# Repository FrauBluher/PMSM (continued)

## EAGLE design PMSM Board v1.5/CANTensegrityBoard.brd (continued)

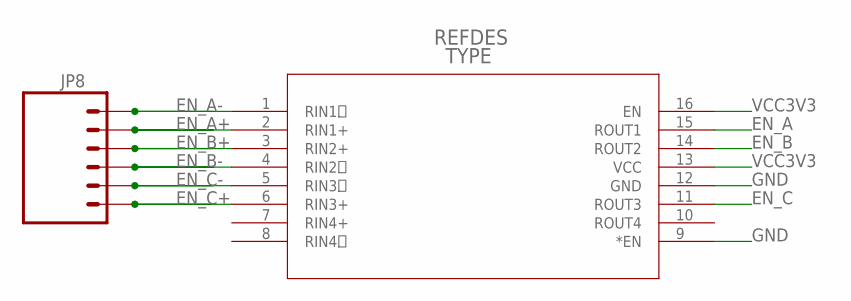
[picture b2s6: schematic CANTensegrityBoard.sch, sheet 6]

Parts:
JP8: M06SIP_LOCK; 1X06-SIP_LOCK
U3: SN65LVDT348_PW_1; PW16

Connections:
EN_A: U3.15 (ROUT1); also elsewhere on the board
EN_A+: JP8.2, U3.2 (RIN1+)
EN_A-: JP8.1, U3.1 (RIN1)
EN_B: U3.14 (ROUT2); also elsewhere on the board
EN_B+: JP8.3, U3.3 (RIN2+)
EN_B-: JP8.4, U3.4 (RIN2)
EN_C: U3.11 (ROUT3); also elsewhere on the board
EN_C+: JP8.6, U3.6 (RIN3+)
EN_C-: JP8.5, U3.5 (RIN3)
GND: U3.9 (*EN), U3.12 (GND); also elsewhere on the board
VCC3V3: U3.13 (VCC), U3.16 (EN); also elsewhere on the board

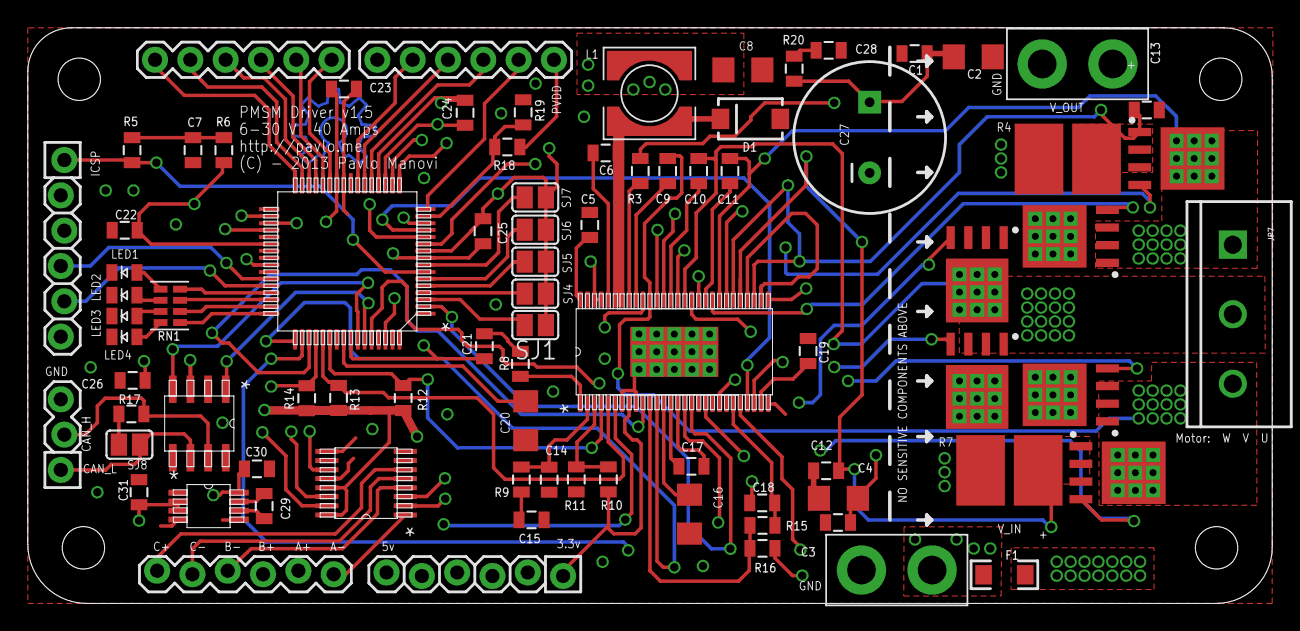
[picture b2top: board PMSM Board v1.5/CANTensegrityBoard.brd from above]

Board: 4 copper layers, 89.5 x 41.4 mm, 87 parts (0 on the bottom side), 94 nets.

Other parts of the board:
E$1, E$2, E$3, E$4: STAND-OFF-TIGHT

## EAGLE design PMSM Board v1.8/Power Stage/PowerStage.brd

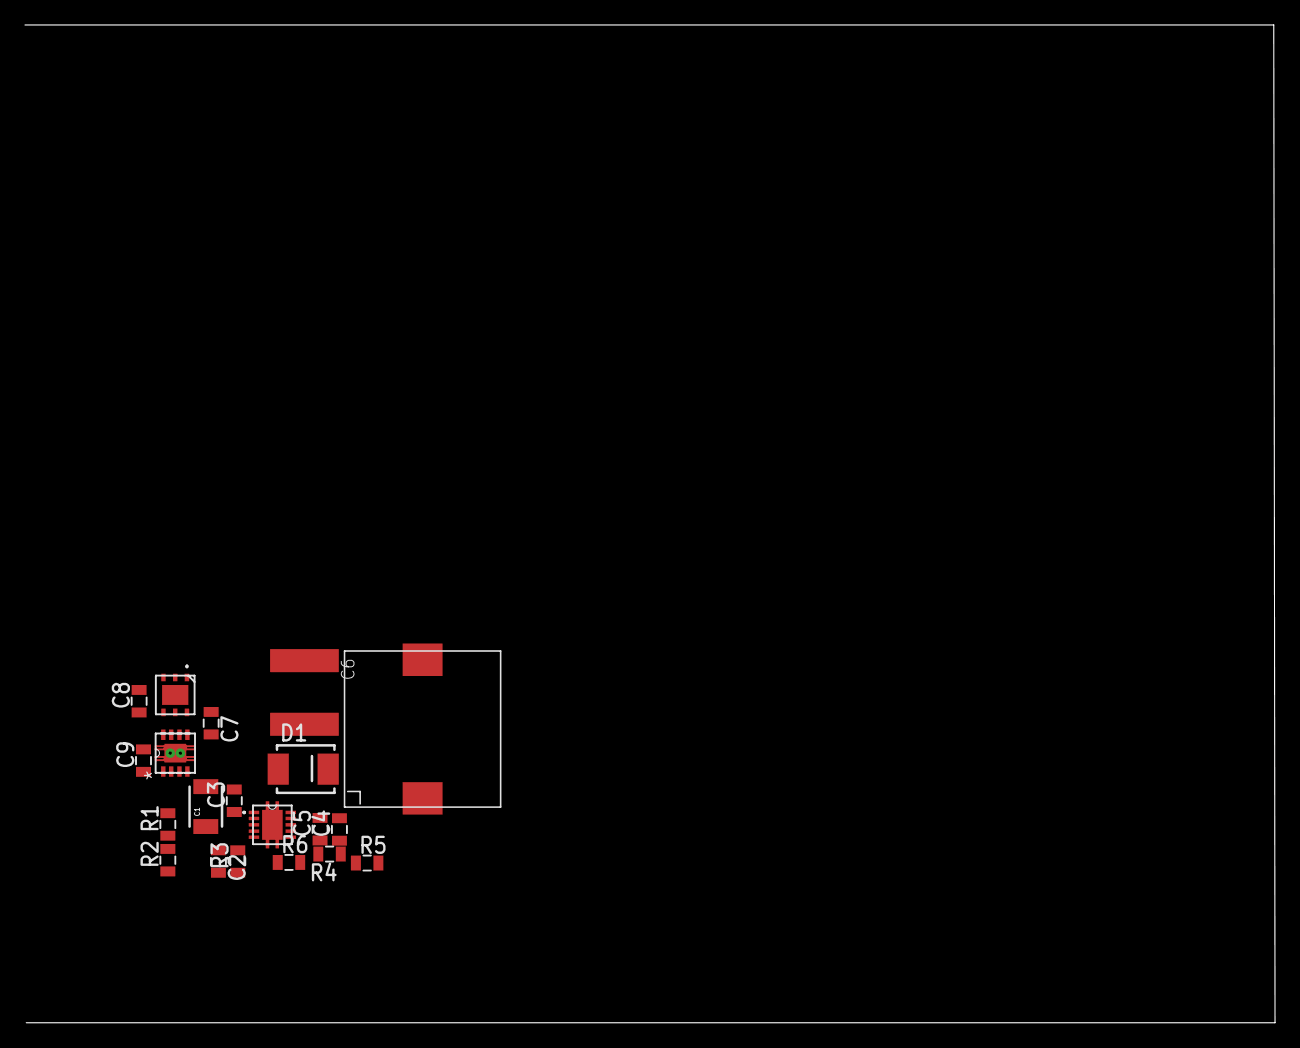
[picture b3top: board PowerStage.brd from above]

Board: 2 copper layers, 100.1 x 79.9 mm, 20 parts (0 on the bottom side), 13 nets, no tracks yet.

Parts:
C1: 4.7uF; 1210
C2: .01uF; 0805
C3: .1uF; 0805
C4: 5600pF; 0805
C5: 270pF; 0805
C6: 47uF\; C2220K
C7, C8, C9: 1uF; 0805
D1: DIODE-SCHOTTKY240A; SMA-DIODE-B240A
R1: 348k; 0805
R2: 88.7k; 0805
R3: 237k; 0805
R4: 7.68k; 0805
R5: 59k; 0805
R6: 10k; 0805
U1: TPS73733-Q1_DRB_8; DRB8_1P75X1P5
U2: TPS54240_DRC_10; DRC10_2P4X1P65
U3: LP38692_NGG_6; SDE06A
U$1: SLF12555T; SLF12555

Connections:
GND: C1.2, C2.2, C4.2, C5.2, C6.2, C7.2, C8.2, C9.2, D1.A, R2.1, R3.1, R6.1, U1.4, U1.9, U2.9, U2.P$1, U2.P$2, U2.P$3, U2.P$4, U2.P$5, U3.2, U3.7
unnamed: R1.1, R2.2, U2.3
unnamed: C2.1, U2.4
unnamed: R3.2, U2.5
unnamed: C3.1, U2.1
unnamed: C3.2, D1.C, U2.10, U$1.P$1
unnamed: C5.1, R4.2, U2.8
unnamed: C4.1, R4.1
unnamed: R5.1, R6.2, U2.7
PVDD: C1.1, R1.2, U2.2
VCC3V3: C9.1, U1.1
VCC5V0: C8.1, U1.5, U1.8, U3.4, U3.5
VCC5V5: C6.1, C7.1, R5.2, U3.1, U3.3, U3.6, U$1.P$2

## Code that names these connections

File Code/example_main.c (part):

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 * dsPIC33EP256MC506:
 *
 * - PIN FUNCTIONS - PIN # - USAGE
 * - RPI44/PWM2H/RB12 - Pin 62 - PWM2
 * - RP42/PWM3H/RB10 - Pin 60 - PWM3
 * - RP97/RF1 - PIN 59 - CANTX (VIA PPS)
 * - RPI96/RF0 - PIN 58 - CANRX (VIA PPS)
 * - RD6 - PIN 54 - PWRGD
 * - RD5 - PIN 53 - OCTW
 * - RP56/RC8 - PIN 52 - FAULT
 * - RP55/RC7 - PIN 51 - GAIN
 * - RP54/RC6 - PIN 50 - EN_GATE
 * - TMS/ASDA1/RP41/RB9 - PIN 49 - DC_CAL
 * - TP40/T4CK/ACL1/RB8 - PIN 48 - LED1
 * - RC13 - PIN 47 - LED2
 * - RP39/INT0/RB7 - PIN 46 - LED3
 * - RPI58/RC10 - PIN 45 - LED4
 * - PGEC2/RP38/RB6 - PIN 44 - PGC
 * - PGED2/RP37/RB5 - PIN 43 - PGD
 * - SDA1/RPI52/RC4 - PIN 36 - EN_A
 * - SCK1/RPI51/RC3 - PIN 35 - EN_B
 * - SDI1/RPI25/RA9 - PIN 34 - EN_C
 * - RPI46/PWM1H/RB14 - PIN 2 - PWM1
 * - AN0/OA2OUT/RA0 - PIN 13 - CRNT1 (Current Sens)
 * - AN1/C2IN1+/RA1 - PIN 14 - CRNT2 (Current Sens)
 *
 *
 * Pins connected to solderjumpers allow for specific ID's to be set on a CAN network with
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 * The following pins and peripherals are available on headers JP1, JP2, and JP5:
 *
 * - PIN FUNCTIONS - PIN # - HEADER,#
 * - AN10/RPI28/RA12 - PIN 11 - JP5,2
 * - AN8/RPI27/RA11 - PIN 12 - JP5,3
 * - AN4/RPI34/RB2 - PIN 17 - JP5,4
 * - AN5/RP35/RB3 - PIN 18 - JP5,5
 *
 * - AN3/OA1OUT/RPI33/STED1/RB1 - PIN 16 - JP2,2
 * - AN6/OA3OUT/C4IN1+/OCFB/RC0 - PIN 21 - JP2,3
 * - AN7/C3IN1-/C4IN1+/RC1 - PIN 22 - JP2,4
 * - AN8/C3IN1+/Y1RTS/BCLK1/FLT3/RC2 - PIN 23 - JP2,5
 *
 * - AN12/C2IN2-/U2RTS/BCLK2/RE12 - PIN 27 - JP1,1
 * - AN13/C3IN20/U2CTS/RE13 - PIN 28 - JP1,2
 * - AN14/RPI94/RE14 - PIN 29 - JP1,3
 * - AN14/RPI95/RE15 - PIN 30 - JP1,4
 * - SDA2/RPI24/RA8 - PIN 31 - JP1,5
 * - FLT32/SCL2/RPI36/RB4 - PIN 32 - JP1,6
 *
 * --Note: RPIx pins can only be remapped to be a peripheral input, while RPx function as I/O.
 */
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#include <stdlib.h>
#include "PMSM.h"

#define LED1 LATBbits.LATB8
#define LED2 LATCbits.LATC13
#define LED3 LATBbits.LATC7
#define LED4 LATCbits.LATC10

#if defined(__dsPIC33EP256MC506__)
_FOSCSEL(FNOSC_FRC & IESO_OFF);
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}

void DigitalPinsInit() {
    TRISDbits.TRISD6 = 1; // PWRGD
    TRISDbits.TRISD5 = 1; // OCTW
    TRISCbits.TRISC8 = 1; // FAULT
    TRISCbits.TRISC7 = 0; // GAIN
    TRISCbits.TRISC6 = 0; // EN_GATE
    TRISBbits.TRISB9 = 0; // DC_CAL
    TRISBbits.TRISB8 = 0; // LED1
    TRISCbits.TRISC13 = 0; // LED2
    TRISBbits.TRISB7 = 0; // LED3
    TRISCbits.TRISC10 = 0; // LED4
    TRISBbits.TRISB14 = 0; // PWM1 Out
    TRISBbits.TRISB12 = 0; // PWM2 Out
    TRISBbits.TRISB10 = 0; // PWM3 Out
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
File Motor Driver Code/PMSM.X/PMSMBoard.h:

/* 
 * File:   PMSMBoard.h
 * Author: Pavlo
 *
 * Created on October 29, 2013, 4:55 PM
 */


#ifndef PMSMBOARD_H
#define	PMSMBOARD_H

#include <xc.h>

#ifdef __33EP256MU806_H
/**
 * @brief Gate Duty Cycle Mapping
 */
#define GL_A_DC       SDC3
#define GH_A_DC       PDC3
#define	GL_B_DC       SDC2
#define GH_B_DC       PDC2
#define GL_C_DC       SDC1
#define GH_C_DC       PDC1

#define TRIS_EN_GATE  TRISGbits.TRISG7
#define TRIS_DC_CAL   TRISEbits.TRISE6
#define TRIS_CS       TRISGbits.TRISG9

#define TRIS_HALL1    TRISCbits.TRISC14
#define TRIS_HALL2    TRISCbits.TRISC13
#define TRIS_HALL3    TRISDbits.TRISD0

#define TRIS_LED1     TRISBbits.TRIB8
#define TRIS_LED2     TRISBbits.TRIB9
#define TRIS_LED3     TRISBbits.TRIB10
#define TRIS_LED4     TRISBbits.TRIB11

#define EN_GATE  LATGbits.LATG7
#define DC_CAL   LATGbits.LATE6
#define CS       LATGbits.LATG9

#define HALL1    PORTCbits.RC14
#define HALL2    PORTCbits.RC13
#define HALL3    PORTDbits.RD0

#define LED1     LATBbits.LATB8
#define LED2     LATBbits.LATB9
#define LED3     LATBbits.LATB10
#define LED4     LATBbits.LATB11
#endif

void UART2Init();
void ClockInit();
void MotorInit();
void TimersInit();
void PinInit();

#endif	/* PMSMBOARD_H */

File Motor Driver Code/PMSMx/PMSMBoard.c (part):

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            CS = 1;
        }
        
        EN_GATE = 0;
        uint16_t i;
        for (i = 0; i < 2000; i++) {
            Nop(); //Let the DRV catch its breath...
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    PTCON = 0x8000;

#endif
    EN_GATE = 1;
    DC_CAL = 0;

    initInfo.MotorInited = 1;
}
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}

void PinInit(void) {
    TRISDbits.TRISD7 = 1; //QEI_A
    TRISDbits.TRISD6 = 1; //QEI_B
    TRISDbits.TRISD5 = 1; //QEI_C

    // 0 - Output, 1 - Input
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
void CNInit(void) {
    //Set up Change Notify Interrupt
    CNENCbits.CNIEC14 = 1; // Enable RC14 pin for interrupt detection
    CNENCbits.CNIEC13 = 1; // Enable RC13
    CNENDbits.CNIED0 = 1;

    IEC1bits.CNIE = 1; // Enable CN interrupts
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
    //AD1CSSH/AD1CSSL: Analog-to-Digital Input Scan Selection Register
    AD1CSSH = 0x0000;
    //AD1CSSLbits.CSS1 = 1;  //PVDD MONITORING
    AD1CSSLbits.CSS12 = 1;
    AD1CSSLbits.CSS13 = 1;

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
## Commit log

2013-07-31 Update LICENSE
2013-08-06 Fixed power and ground issue on the decoupling caps
2013-09-04 Refactored some code and added a boilerplate to work off of.
2013-09-04 Update example_main.c
    Added some suggestions.
2013-09-24 Redesign of board to incorporate new TI rec. design, added filtering.
2013-09-24 Added some test points and cleaned up v1.6
2013-09-25 Removed thermals in a few places.
2013-10-01 Generated gerbers and moved a power trace.
2013-10-29 Working copy backup. Started some serious software driver/integration work.
2013-10-30 Made everything more modular and added DRV8301 Driver Code.
2014-01-07 1.7 Progress
2014-01-07 Power Stage Folder added to version 1.7 Folder
2014-01-08 More switcher work.
2014-01-10 rerouting PMSM Board
2014-01-10 Started making room for connectors
2014-01-10 More redesign work for v1.7
2014-01-13 Almost done with v1.7~
2014-01-13 Finished v1.7
2014-01-13 Choring up the repo.
2014-01-13 Added DRV830x Library
2014-01-13 Fixed CAN Connector Pinout
2014-01-13 Fixed Optical Encoder Output
2014-02-12 Fixed file paths.
2014-03-04 Choring up code for v1.7.
2014-03-11 SPI Library now works and is 100% tested for drv8303
2014-03-22 v1.7 Basic Functionality Snapshot
2014-05-07 Started board version 1.8
2014-05-08 Completed v1.8 of PMSM Board.
2014-06-24 Completed Board v1.9
2014-07-11 Motor control work and board dimension corrections.
2014-07-23 Config Tool and Code Cleanup
2014-08-03 Controls work.
2014-08-04 Embedded matplotlib into the config tool.
2014-08-18 Board v1.9b and SystemID work.
2014-08-20 Added working LQG controller for Maxon Motor
2014-09-02 Lots of FOC work.
2014-09-02 FOC working.
2014-09-03 More FOC Work.
2014-09-08 Added CAN testing project to verify the operation of the CAN modules.
2014-09-09 This holds a working copy of Motor Board Testing Can project
2014-09-09 Added the Can Festival Code base for working CAN testing code
2014-09-10 CAN Festival now working in CAN example code.
2014-09-19 Working LQG Position Control.
2014-09-20 CAN working on MOTOR board
2014-09-21 Updated PMSM.c with LQG Controller.
2014-09-21 Trying to merge with master....
2014-09-22 Code Styling, Documentation.
2014-09-23 PMSM.c Compiles.
2014-09-23 Updated some documentation.
2014-09-24 testing the new Postition controller seems to not be working properly?
2014-09-24 Added theta1 for PMSM_Init
2014-09-24 Chaned the PMSM.c file to work with Motor 7 Hopefully this will work on the other motors?
2014-09-24 Modified PMSM code to compile with CAN (again) - Haven't tested yet on this commit
2014-09-24 Added the pin defines for CAN1 on the PIC.
2014-09-28 Modified to start controlling the motor over can
2014-09-28 Added cable length and velocity methods. Event loops runs at 15kHz now.
2014-09-28 Added QEI Update to event loop.
2014-09-28 started implementing an impedance controller on the motor board
2014-09-29 Still implementing a impedence contoller.... not done yet
2014-09-29 added a .gitignore file to the project. It doesn't work retro-actively, but can be used to update the system later on Will effect newly added files
2014-09-29 Added my folder which the CAN_Testing branch uses. This project will not compile correctly if you are not on the CAN_Testing Branch
2014-10-01 Working on a impedance controller, this has an OK(?) PD controller on motor
2014-10-01 Kind of works... I think. Oscillates a lot, but does what I think it should do??
2014-10-01 Working on figuring out a QEI issue
2014-10-02 Trying to make something work on controls
2014-10-02 Got rid of some junk files with a .*~ ending.
2014-10-02 Messing with intial parameters
2014-10-02 Pavlo worked on getting DRV error codes to output over UART
2014-10-06 Remved all the MPLabX build files from PMSMx's index
2014-10-06 Removed all the text editor backup files (~) from the repo
2014-10-06 Edited the old code that cropped up in merger..... :-/
2014-12-02 Re-ID of motors and state-space implementation of controls.
2014-12-11 Major Refactor, new Controllers Pos/Vel, documentation needs updating.
2015-02-04 Changes made a while ago for the CANTesting branch
2015-02-05 disabled config settings to allow the code to be used with a bootloader
2015-02-05 Modified the CAN objectdic files
2015-02-05 Changed the #include to correct path for data.h in objectdic.h
2015-02-05 Changed the naming for CAN motor position variable
2015-02-06 Stuff
2015-02-07 EN_GATE refactoring.
2015-02-07 Stopped tracking compiled files.
2015-02-13 Working on getting Torque controll
2015-02-13 Added an updated object dictionary for CANOpen
2015-02-13 Added CAN Impdeance characterization stuff
2015-02-13 Added PRBSData.h
2015-02-17 Working to get ICRA data
2015-02-19 Modified code to accept position data from ROS network with consisten units as it outputs milli-radians
2015-02-20 SStuff
2015-02-20 Lowered PWM frequency, and modified dead-time correction settings.
2015-02-20 Modified for new Position Controller testing
2015-02-21 New position controller.
2015-02-21 Another new motor position controller.
2015-02-21 Motor Board proportional controller.
2015-02-23 Revert "Another new motor position controller."
    This reverts commit 22a5d82d473f195f83678fc6334c705e9404d4e3.
2015-02-24 Added new objdict files for Motor Boards 2 and 72
2015-02-24 Updating canopen files
2015-02-25 Changed the CAN objdict files
2015-02-26 Updated the objdict files
2015-02-26 new objcdict stuff
2015-02-26 This code works without CAN....
2015-02-26 Works with CAN!
2015-02-26 Now working with config builds for 2 and 72 boards
2015-02-26 Updated heartbeat messages in objdict
2015-03-06 Changes to the can controller and the CANOpen files
2015-03-06 Decoupled commuation and control.
2015-03-06 Added objdict 72 files
2015-03-07 CLID Work.
2015-03-07 Changed objdict for Motor testing
2015-03-07 Code now compiles.
2015-03-09 Updated the latest code with the new CANOpen Objdicts
2015-03-09 Switched from testing data to position
2015-03-09 Updated the .h objdict 2
2015-03-09 Trying to figure out why Position isn't working
2015-03-19 Modified the motor controller to be a P gain controller. Also updating commutation at controller update speed, not 15kHz.
2015-04-08 WOrking on impedance controller
2015-04-25 Fixed point SVM working, commutation runs at 15kHz.
2015-04-25 Added fixed point SVM library file.
2015-05-19 Got CAN working and made changes so that CAN wont write over itself
2015-07-31 Working on various things. mainly trying to get 5.5v working
2015-08-13 Making minor changes to get 100 power on superball
2015-08-13 Fixed to work with both boards 2 and 72
2016-01-09 Added a bunch of stuff
2016-01-20 CAN and PMSM driver are conflicting....
2016-01-21 Changed the timer_dspic.c file to match the ones used on Sensor and Power boards
2016-01-21 added hack to main.c to fix CAN interrupt issue. main now calls _C1Interrupt() as fast as possible
2016-01-22 Fixed motor board CAN and timing issues. Reduced control loop frequency to 10KHz.
2016-01-23 updated motor 72 object dictionary
2016-01-23 added watchdog timer (hack) for the CAN interrupt
2016-01-27 Got motor drivers working with constant control at 10kHz
